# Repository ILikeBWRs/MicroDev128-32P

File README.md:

### *Thank You to PCBWay for sponsoring this project! To see more look up the "Sponsorship Section"*

---

Main Project Page:[MicroDev128 project](https://github.com/ILikeBWRs/MicroDev128)

---

# MicroDev128-32P
## A high-power development/prototyping board with MVIO. 

Based on the AVR128DB32. 

The MicroDev128-32P is open-source development board with a high-power voltage regulator with up to 2A continous, Multi-voltage IO - which allows PortC to run on a different voltage than the rest of the board - elimenating the need for voltage level shifters. The MicroDev128-32P aims to be better price to performance ratio than a tradition Arduino Nano. To view the Schematics you can go into the Kicad files folder. All files were made on KiCad 10.04 and should import without other dependencies. The 3D models are all included in the folder. 

**Key Specifications:**
- Up to 2A continuos on both power lines, 3.3v and 5v with up to 42VDC input
- Arduino Nano sized footprint, allowing it to easily be plugged into breadboards
- 128kB Flash, 16kB SRAM, and 512B EEPROM
- Has with internal clock adjustable up to 24MHz max
- Built in reverse polarity protection, fuse and overcurrent/short protection
- UPDI Header for programming 
- Onboard LED and 3 programble, seperatly adressable NeoPixels

## Documentation

For Documentation see the MicroDev128 Docs repository. This includes technical information such as regulator ripple, tests etc. 
[Link to Documents](https://github.com/ILikeBWRs/MicroDev128-Documentation)

---

## Images

---

## Ordering

To order your own you have a few ways:

**1. Order Blank PCBs and assemble them yourself**

*You will need a hotplate for solder reflow and solder paste. May be cheaper but harder to do!*

Upload the Gebers at:
/MicroDev128-32P Production Files
   /Gebers.zip
Go to PCBWay's online ordering page and upload the gebers. Make sure it says 4-layers. Set it to ENIG, and set the solder mask to any colour you want. The rest of the default settings will be fine. Hit order or add stencil if you need one. It's that easy!

Next in the same folder find the BOM.csv and order the parts from your favorite part distributor. 
To lay out components once they turn up you can use the KiCad PCB layout. A dedicated image for this step will come later.

**2. Use PCBWay's PCBA service and get them shipped assembled**

Upload the Gebers at:

/Production Files

   /Gebers.zip
   
Go to your PCB and upload the gebers. Make sure it says 4-layers. Set it to ENIG, and set the solder mask to any colour you want. The default settings will be fine.
Then upload the BOM.csv and CPL.csv to the page. Then check if they in stock. (You may need to pre-order some parts!)
The check component orientation - it has a tendency to flip the LT8653S by 90 degrees. 
Then pay and let PCBWay's professional automated factory ship them fully assembled, right to your door!

---

## Revision Information

This repository was last updated: *2026-09-12*

This design is revision: *1B*

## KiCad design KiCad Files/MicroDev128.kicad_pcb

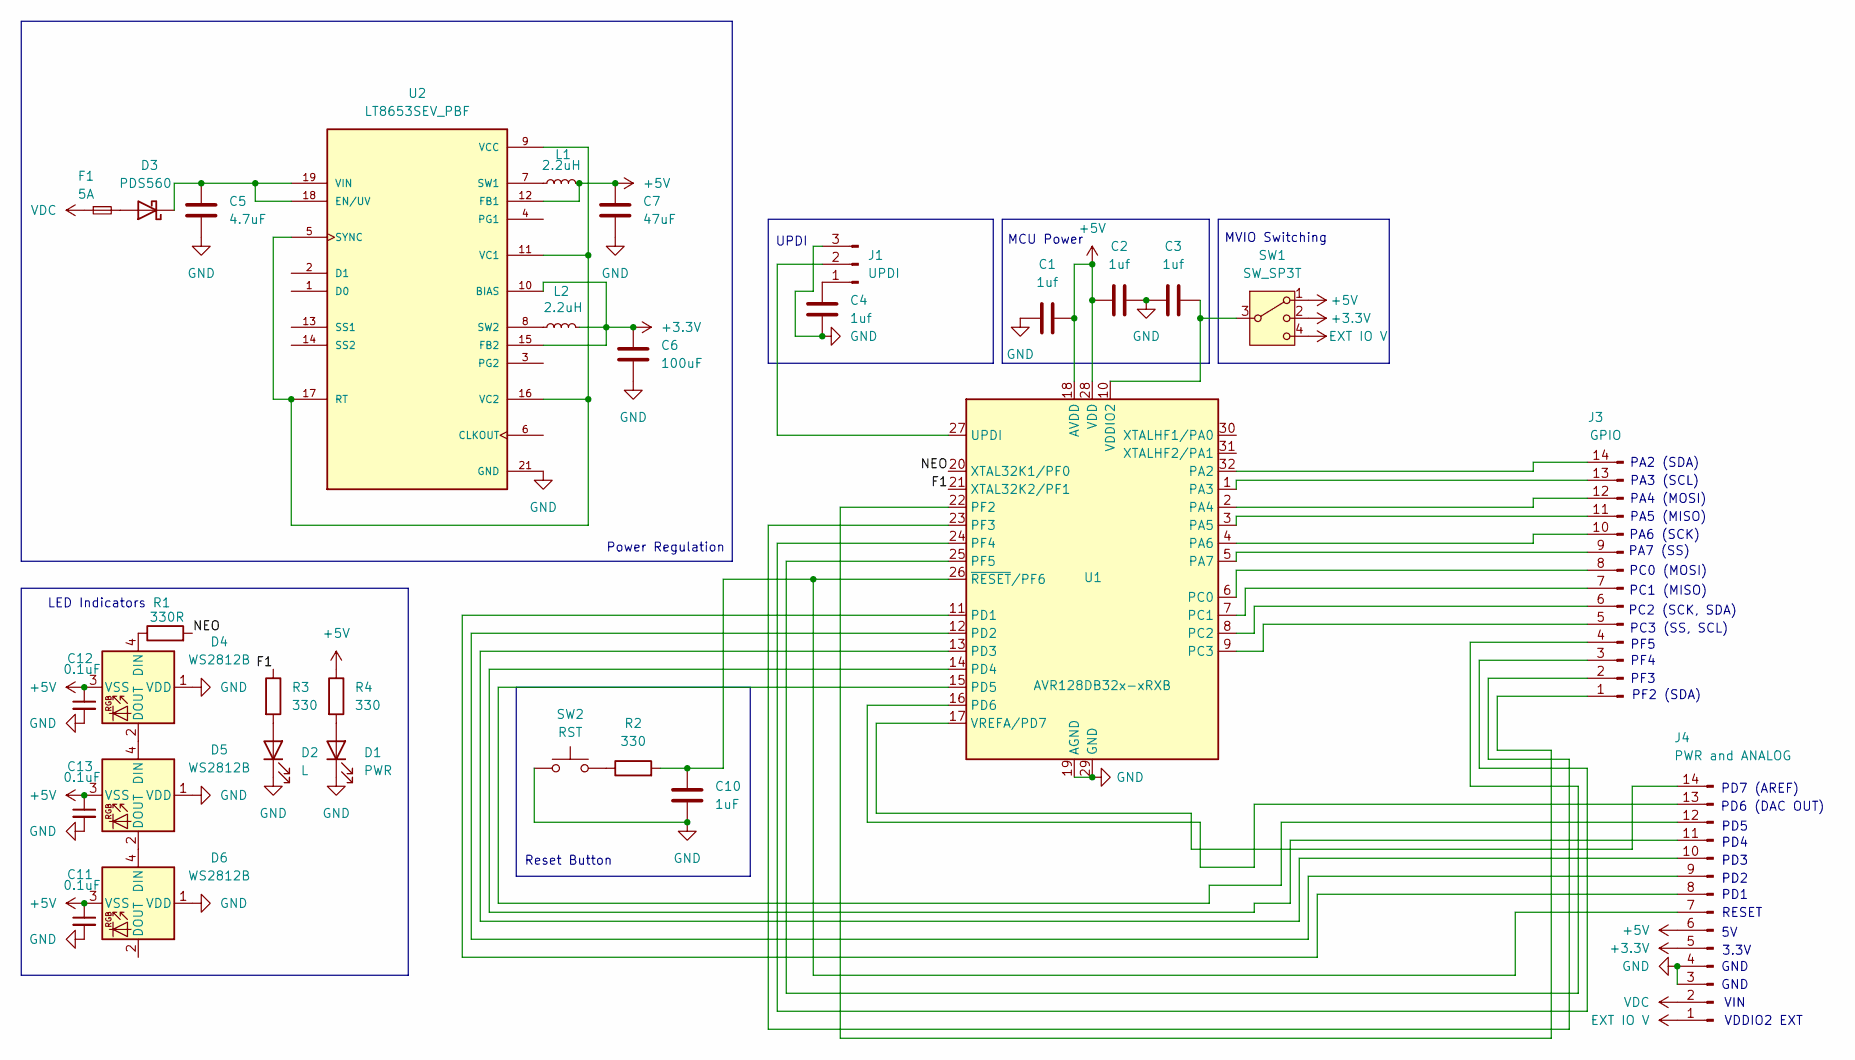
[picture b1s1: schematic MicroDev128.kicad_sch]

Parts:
C1, C2, C3, C4: 1uf; C_0603_1608Metric
C5: 4.7uF; C_1206_3216Metric
C6: 100uF; C_1206_3216Metric
C7: 47uF; C_1206_3216Metric
C10: 1uF; C_0603_1608Metric
C11, C12, C13: 0.1uF; C_0402_1005Metric
D1: PWR; LED_0603_1608Metric
D2: L; LED_0603_1608Metric
D3: PDS560; D_PowerDI-5
D4, D5, D6: WS2812B; LED_WS2812B-2020_PLCC4_2.0x2.0mm
F1: 5A; Fuse_0603_1608Metric
J1: UPDI; PinHeader_1x03_P2.54mm_Vertical
J3: GPIO; PinHeader_1x14_P2.54mm_Vertical
J4: PWR and ANALOG; PinHeader_1x14_P2.54mm_Vertical
L1, L2: 2.2uH; L_Taiyo-Yuden_NR-40xx
R1: 330R; R_0402_1005Metric
R2, R3, R4: 330; R_0402_1005Metric
SW1: SW_SP3T; SW_SP3T_PCM13
SW2: RST; SW_Push_1P1T_NO_CK_KMR2
U1: AVR128DB32x-xRXB; QFN-32-1EP_5x5mm_P0.5mm_EP3.1x3.1mm
U2: LT8653SEV_PBF; QFN-20-1EP_3x4mm_P0.5mm_EP1.65x2.65mm; PARTREV B

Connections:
+3.3V: C6.1, J4.5, L2.2, SW1.2, U2.10 (BIAS), U2.15 (FB2)
+5V: C1.2, C2.1, C7.1, C11.1, C12.1, C13.1, D4.3 (VSS), D5.3 (VSS), D6.3 (VSS), J4.6, L1.2, R4.1, SW1.1, U1.18 (AVDD), U1.28 (VDD), U2.12 (FB1)
/F1: R3.1, U1.21 (XTAL32K2/PF1)
/NEO: R1.2, U1.20 (XTAL32K1/PF0)
EXT IO V: J4.1, SW1.4
GND: C1.1, C2.2, C3.1, C4.2, C5.2, C6.2, C7.2, C10.2, C11.2, C12.2, C13.2, D1.1 (K), D2.1 (K), D4.1 (VDD), D5.1 (VDD), D6.1 (VDD), J1.3, J4.3, J4.4, SW2.1, U1.19 (AGND), U1.29 (GND), U1.33 (GND), U2.21 (GND)
unnamed: D1.2 (A), R4.2
unnamed: D2.2 (A), R3.2
unnamed: D3.2 (A), F1.2
unnamed: C5.1, D3.1 (K), U2.18 (EN/UV), U2.19 (VIN), U2.20 (VIN)
unnamed: D4.4 (DIN), R1.1
unnamed: D4.2 (DOUT), D5.4 (DIN)
unnamed: D5.2 (DOUT), D6.4 (DIN)
unnamed: C4.1, J1.1
unnamed: J1.2, U1.27 (UPDI)
unnamed: J3.1, U1.22 (PF2)
unnamed: J3.2, U1.23 (PF3)
unnamed: J3.3, U1.24 (PF4)
unnamed: J3.4, U1.25 (PF5)
unnamed: J3.5, U1.9 (PC3)
unnamed: J3.6, U1.8 (PC2)
unnamed: J3.7, U1.7 (PC1)
unnamed: J3.8, U1.6 (PC0)
unnamed: J3.9, U1.5 (PA7)
unnamed: J3.10, U1.4 (PA6)
unnamed: J3.11, U1.3 (PA5)
unnamed: J3.12, U1.2 (PA4)
unnamed: J3.13, U1.1 (PA3)
unnamed: J3.14, U1.32 (PA2)
unnamed: C10.1, J4.7, R2.2, U1.26 (~RESET/PF6)
unnamed: J4.8, U1.11 (PD1)
unnamed: J4.9, U1.12 (PD2)
unnamed: J4.10, U1.13 (PD3)
unnamed: J4.11, U1.14 (PD4)
unnamed: J4.12, U1.15 (PD5)
unnamed: J4.13, U1.16 (PD6)
unnamed: J4.14, U1.17 (VREFA/PD7)
unnamed: R2.1, SW2.2
unnamed: C3.2, SW1.3, U1.10 (VDDIO2)
unnamed: U2.5 (SYNC), U2.9 (VCC), U2.11 (VC1), U2.16 (VC2), U2.17 (RT)
unnamed: L1.1, U2.7 (SW1)
unnamed: L2.1, U2.8 (SW2)
VDC: F1.1, J4.2

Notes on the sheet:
PD5
PC2 (SCK, SDA)
LED Indicators
GND
PA5 (MISO)
3.3V
UPDI
PD3
Reset Button
PF4
PA7 (SS)
PC0 (MOSI)
PD2
VIN
PF2 (SDA)
PF3
PA4 (MOSI)
RESET
PD6 (DAC OUT)
PF5
PA2 (SDA)
Power Regulation
PA6 (SCK)
PC1 (MISO)
MVIO Switching
VDDIO2 EXT
PD7 (AREF)
PA3 (SCL)
PD1
PC3 (SS, SCL)
PD4
MCU Power
GND

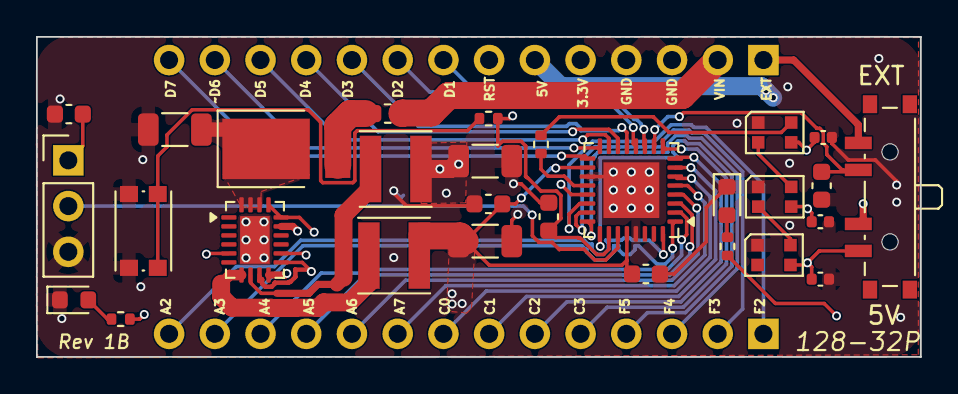
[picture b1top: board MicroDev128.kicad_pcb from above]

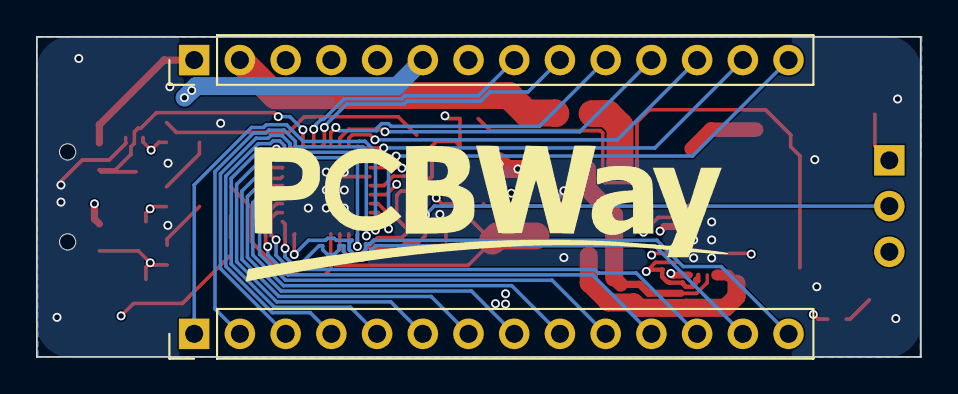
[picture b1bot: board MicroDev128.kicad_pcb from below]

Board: 4 copper layers, 49.1 x 17.8 mm, 31 parts (2 on the bottom side), 43 nets.

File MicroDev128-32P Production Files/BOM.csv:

Ref Des,Footprint,Quantity,Designation,Manufacturer,Mfg Part#,Desciption/Value,Package,Type,Notes
"C1, C2, C3, C4",C_0603_1608Metric,4,1uf,Yageo,CC0603KRX5R6BB105,"1uF 0603 X5R, ±10%",603,SMD,Not strict – generic options will work fine if they match the specifications. 
C5,C_1206_3216Metric,1,4.7uF,Murata,GRM31CC72A475KE11K,4.7uF 1206 ±10% X7S,1206,SMD,
C6,C_1206_3216Metric,1,100uF,Murata,GRM31CR60J107ME39L,"100µF, 6.3V, ±20% X5R",1206,SMD,
C7,C_1206_3216Metric,1,47uF,Murata,GRM31CR61A476ME15L,"47µF, 10V, ±20% X5R",1206,SMD,
C10,C_0603_1608Metric,1,1uF,Yageo,CC0603KRX5R6BB105,"1uF 0603 X5R, ±10%",603,SMD,
"C11, C12, C13",C_0402_1005Metric,3,0.1uF,Murata,GRM155R71A104KA01D,0.1uF 402 ±10% X7R,402,SMD,
D1,LED_0603_1608Metric,1,PWR,Everlight,19-217/R6C-AL1M2VY/3T,Standard Red SMD Led,603,SMD,
D2,LED_0603_1608Metric,1,L,Everlight,19-217/R6C-AL1M2VY/3T,Standard Red SMD Led,603,SMD,
D3,D_PowerDI-5,1,PDS560,Diodes Incorporated,PDS560-13,Schottky 60V 5A,PowerDI-5,SMD,
"D4, D5, D6",LED_WS2812B-2020_PLCC4_2.0x2.0mm,3,WS2812B,Worldsemi,WS2812B-2020,"RGB with IC, 5V, 2.0x2.0mm 
",PLCC-4,SMD,
F1,Fuse_0603_1608Metric,1,5A,Bourns,SF-0603F500-2,"5A, 32V, Fast-Acting",603,SMD,
J1,PinHeader_1x03_P2.54mm_Vertical,1,UPDI,DNP,DNP,DNP,DNP,DNP,No Not Place
J3,PinHeader_1x14_P2.54mm_Vertical,1,GPIO,DNP,DNP,DNP,DNP,DNP,No Not Place
J4,PinHeader_1x14_P2.54mm_Vertical,1,PWR and ANALOG,DNP,DNP,DNP,DNP,DNP,No Not Place
"L1, L2",L_Taiyo-Yuden_NR-40xx,2,2.2uH,Taiyo Yuden,NR4018T2R2M,"2.2µH, ±20%, 2.70A
",4.0x4.0mm ,SMD,
R1,R_0402_1005Metric,1,330R,Yageo,RC0402FR-07330RL,330Ohm 1% 1/16W Metal film resistor,402,SMD,
"R2, R3, R4",R_0402_1005Metric,3,330R,Yageo,RC0402FR-07330RL,330Ohm 1% 1/16W Metal film resistor,402,SMD,
SW1,SW_SP3T_PCM13,1,SW_SP3T,C&K / Littelfuse,PCM13SMTR,"Slide, SP3T, 3-Position, 0.3A 6VDC",PCM13,SMD,
SW2,SW_Push_1P1T_NO_CK_KMR2,1,RST,C&K / Littelfuse,KMR221G LFS,"SPST-NO, Top Actuated, 50mA 32VDC",4.6x2.8mm,SMD,
U1,QFN-32-1EP_5x5mm_P0.5mm_EP3.1x3.1mm,1,AVR128DB32x-xRXB,Microchip Technology,AVR128DB32-E/RXB,"AVR Microcontroller, 128kB Flash",QFN-32,SMD,
U2,QFN-20-1EP_3x4mm_P0.5mm_EP1.65x2.65mm,1,LT8653SEV_PBF,Analog Devices,LT8653SEV#PBF,Silent Switcher2 High Power Buck Reg,QFN-20,SMD,
